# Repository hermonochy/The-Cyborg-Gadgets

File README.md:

***SPDX-License-Identifier:*** *CC-BY-NC-SA-4.0*

# The Cyborg Gadgets

The Cyborg Gadgets are a project to develop non-invasive, painless body enhancements. 
It is highly beneficial to have all essential tools with you, make the impression to be very smart, and deter adversaries of low intelligence. 

These gadgets can take on any form, however tend to be built on or as everyday wearable objects, such as watches.

## Labeling

The gadgets are all labeled, as seen in the example below:

- **Generation**: The cyborg tools are split into successive generations, depending on the type of technology being utilised:

    - The single [Generation 0](./Generation_0/Generation_0.md) gadget is a simple AA battery powered multitool using crocodile clips rather than switches to create a simple multitool gadget. 
    While not a true body extension, it did provide the inspiration for this project and is therefore counted as the first cyborg extension.
    - [Generation 1](./Generation_1/Generation_1.md) featured a simple parallel circuit on a circuit board, introducing switches and using a LiPo battery for size. 
    - The [Second generation](./Generation_2/Generation_2.md) still retained the same circuit, however was built with wires rather than a prototype board. 
    This enhanced its lifespan from roughly 3 weeks to more than 2 years, while also making assembly easier. Currently they are the largest generation, with over a dozen operational gadgets.
    - [The Third Generation](./Generation_3/Generation_3.md) relies on the Arduino platform to drastically enhance capabilities to include smart, multifunctional spy features. Surprisingly, energy consumption is reduced.
    - [Generation 4](./Generation_4/Generation_4.md) devices are electronically identical to the third but use customised PCBs and refined mechanical designs to improve aesthetics and stability.
    - [Fifth generation](./Generation_5/Generation_5.md) cyborg gadgets switch from [AVR based microcontrollers](https://en.wikipedia.org/wiki/Atmel) to [ESP32](https://www.espressif.com/en/products/socs/esp32-c3) based chips, significantly improving proccessing capabilities while retaining small form factor.
    - Sixth Generation devices use ESP's like the 5th, but are sturdier, more feature rich and more compact than the 5th generation on account of using specialised boards with builtin features.
    - [The Seventh Generation](./Generation_7/Generation_7.md) hasn’t been fully defined yet, but the LicheeRV Nano is a promising candidate for its microcontroller. Since the ESP32 devices used in the fifth and sixth generations already exceed the performance requirements at the present time, there is no immediate pressure to launch a Seventh Generation.

- **Type of gadget**: While originally focused on watch extensions, the project now includes devices for:

    - Watches
    - Badges
    - Gloves
    - Necklaces
    - Shoes
    - Bags

- **Induvidual number**: Within each generation and gadget type, every device is given a unique number, typically assigned in order of production.

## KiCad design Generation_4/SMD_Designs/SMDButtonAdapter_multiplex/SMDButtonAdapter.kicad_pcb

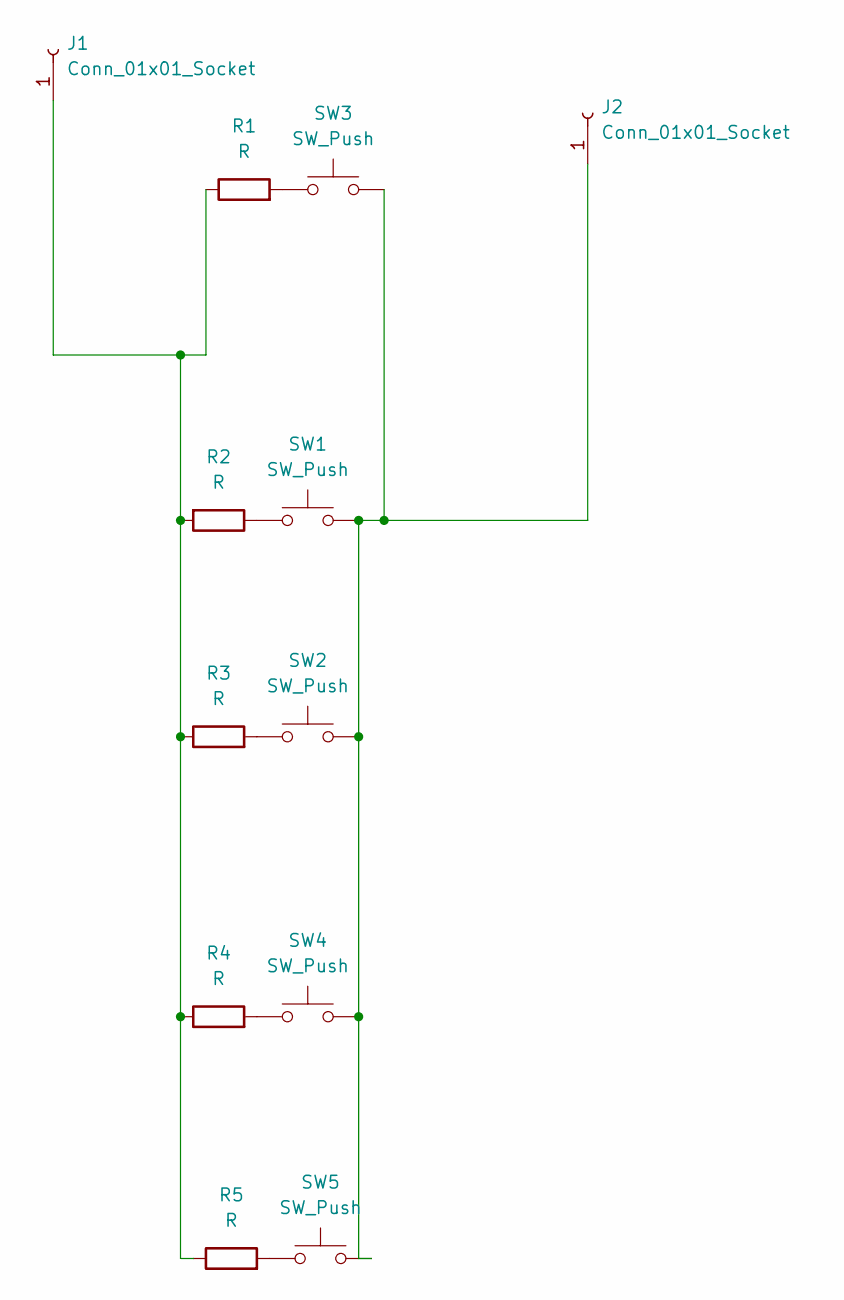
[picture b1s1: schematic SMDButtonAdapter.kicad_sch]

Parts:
J1, J2: Conn_01x01_Socket; Pin_D1.3mm_L11.0mm_LooseFit
R1, R2, R3, R4, R5: R; R_1206_3216Metric
SW1, SW2, SW3, SW4, SW5: SW_Push; SW_SPST_SKQG_WithStem

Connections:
unnamed: J1.1, R1.1, R2.2, R3.1, R4.1, R5.1
unnamed: J2.1, SW1.2, SW2.2, SW3.2, SW4.2, SW5.2
unnamed: R1.2, SW3.1
unnamed: R2.1, SW1.1
unnamed: R3.2, SW2.1
unnamed: R4.2, SW4.1
unnamed: R5.2, SW5.1

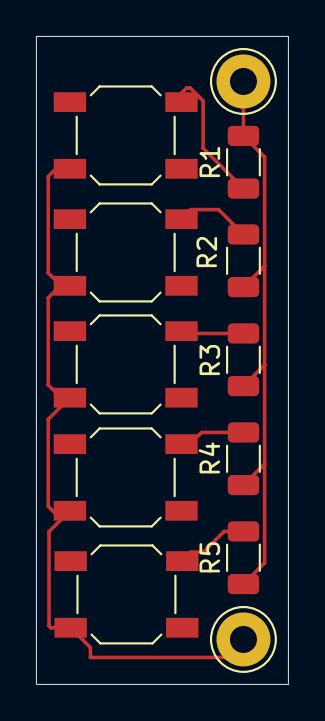
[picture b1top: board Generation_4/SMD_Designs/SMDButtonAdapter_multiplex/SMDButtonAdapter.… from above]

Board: 2 copper layers, 14.0 x 36.0 mm, 12 parts (0 on the bottom side), 7 nets.

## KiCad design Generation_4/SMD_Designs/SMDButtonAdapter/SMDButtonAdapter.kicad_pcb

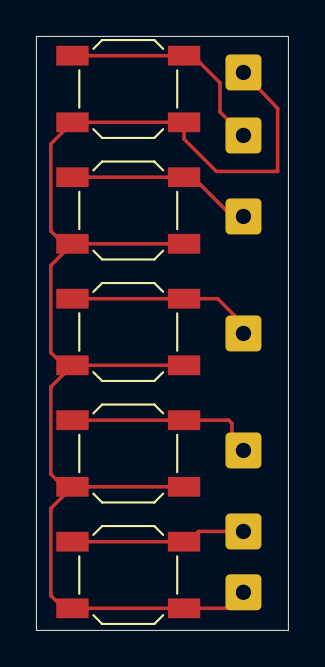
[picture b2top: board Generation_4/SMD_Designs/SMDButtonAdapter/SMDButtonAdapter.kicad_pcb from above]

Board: 2 copper layers, 14.0 x 33.0 mm, 12 parts (0 on the bottom side), 6 nets.

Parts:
J1, J2, J3, J4, J5, J6, J7: Conn_01x01_Socket; SolderWire-0.25sqmm_1x01_D0.65mm_OD2mm
SW1, SW2, SW3, SW4, SW5: SW_Push; SW_SPST_SKQG_WithStem

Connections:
unnamed: J1.1, SW1.1
unnamed: J2.1, SW2.1
unnamed: J3.1, SW3.1
unnamed: J4.1, SW4.1
unnamed: J5.1, SW5.1
unnamed: J6.1, J7.1, SW1.2, SW2.2, SW3.2, SW4.2, SW5.2

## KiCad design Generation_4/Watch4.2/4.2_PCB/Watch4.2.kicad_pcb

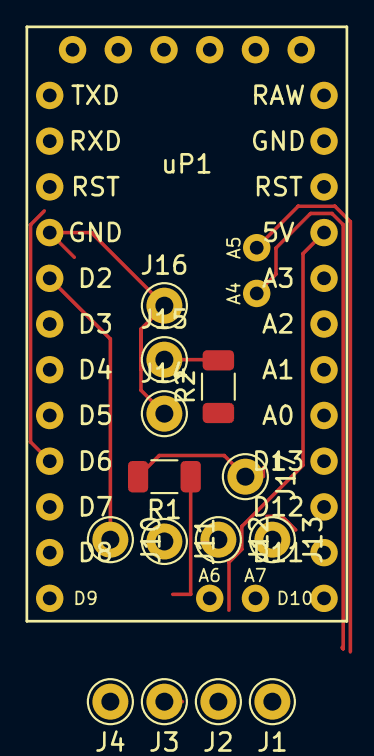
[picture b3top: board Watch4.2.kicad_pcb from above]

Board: 2 copper layers, 15 parts (0 on the bottom side), 10 nets.

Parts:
J1, J2, J3, J4, J10, J11, J12, J13, J14, J15, J16, J17: Conn_01x01_Socket; Pin_D1.0mm_L10.0mm
R1, R2: R; R_1206_3216Metric
uP1: ProMini2; Pro_Mini

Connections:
unnamed: J1.1, uP1.31 (PA4)
unnamed: J2.1, uP1.32 (PA5)
unnamed: J3.1, uP1.22 (Vcc/5v)
unnamed: J10.1, uP1.11 (PD2)
unnamed: J11.1, uP1.13 (PD4)
unnamed: J12.1, uP1.14 (PD5)
unnamed: J13.1, uP1.12 (PD3)
unnamed: J4.1, J14.1, J16.1, R1.1, R2.1, uP1.10 (GND)
unnamed: J15.1, R2.2, uP1.15 (PD6)
unnamed: J17.1, R1.2

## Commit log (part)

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2025-10-29 Update Gen 3 watches
2025-10-30 Add 3.8 and update 3.2
2025-11-10 Update gen 3
2025-12-14 Update 3rd and 4th gen descriptions and fix bugs
2026-02-21 Begin work on 5th gen
2026-02-23 Working 5.0 progrsm
2026-02-23 Add wifi capability to 5.0
2026-02-24 Minor tweaks to wifi and weather
2026-02-26 Add serial version for notepad in 5.0
2026-02-26 Add settings, launch calculator and unit converter with maths function
2026-02-27 Add graph plotter to 5.0
2026-03-02 Add more games
2026-03-06 Reintregrate debug to 5.0
2026-03-06 Split 5.0 into seperate files
2026-03-06 Add geo dash game to 5.0
2026-03-07 Add multiple network support to 5.0
2026-03-08 Update Gen 5
2026-03-10 Add base converter and button tuning to 5.0
2026-03-14 Modify 5.0 debug func
2026-03-23 Tidy up of code and UI
2026-03-23 Add funcs to 5.0: disconnect wifi, scan wifi networks
2026-03-23 Add shell to 5.0
2026-03-24 Add calendar to 5.0
2026-03-27 Fix minor bugs
2026-03-29 Add Watch 3.3 (currently very buggy)
2026-03-30 Move some variables to specific modules
2026-04-10 Add issue and pull request templates
2026-04-10 Game in Watch 3.3 is now playable
2026-04-10 Add Gen 7
2026-04-23 Fix time sync
2026-04-23 Add if and while to shell
2026-04-26 Add time settings
2026-04-27 Minor UI tweaks
2026-04-30 Add discionary and improve metronome
2026-04-30 Save and load buttons from NVS in 5.0
2026-04-30 add blink settings to 5.0
2026-05-17 Add new function to settings.ino: Btn Settings
2026-05-18 Improve main UI
2026-05-18 Restructure games menu
2026-05-20 Fix minor bugs, add new features - Matrix calculator (not yet fully functional) - Prime Factorisation calculator - Minor bug fixes and GUI tweaks
2026-05-28 Initial Watch 5.1 [not yet working]
2026-05-28 add initial 5.1 [not working]
2026-05-28 5.1: improve UI [not working]
2026-05-28 Working Main and Setup on Watch 5.1
2026-05-28 Minor tweaks to 5.0
2026-05-28 clean up Gen 4
2026-05-28 Fix 5.1 files
2026-05-30 Further tweaks to 5.1 UI
2026-06-01 Add more UI fixes to 5.1
2026-06-02 Wifi fix, light sleep mode working, switch light/dark mode
2026-06-08 minor tweaks to 5.1
2026-06-16 Update 5.1: improve main UI
2026-06-24 Can now customise colours in 5.1
